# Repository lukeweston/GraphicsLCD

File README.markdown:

Breakout board or interface board for LCD displays.

Intended mainly for KS0108-compatible graphical LCD displays or similar. (Usually 128 x 64 pixels.)

This board allows you to connect a LCD display of this sort to your host microcontroller using a minimal number of pins - and also offloading the processing and memory usage
associated with driving the display away from the host microcontroller and onto the display microcontroller. Based on the Atmel ATmega32U4 (Arduino Leonardo-compatible)
microcontroller.

Serial data is supplied to the microcontroller over either the USB, TTL-level UART, SPI or I2C interfaces - whatever you want. 5V power must also be supplied from the host
microcontroller.

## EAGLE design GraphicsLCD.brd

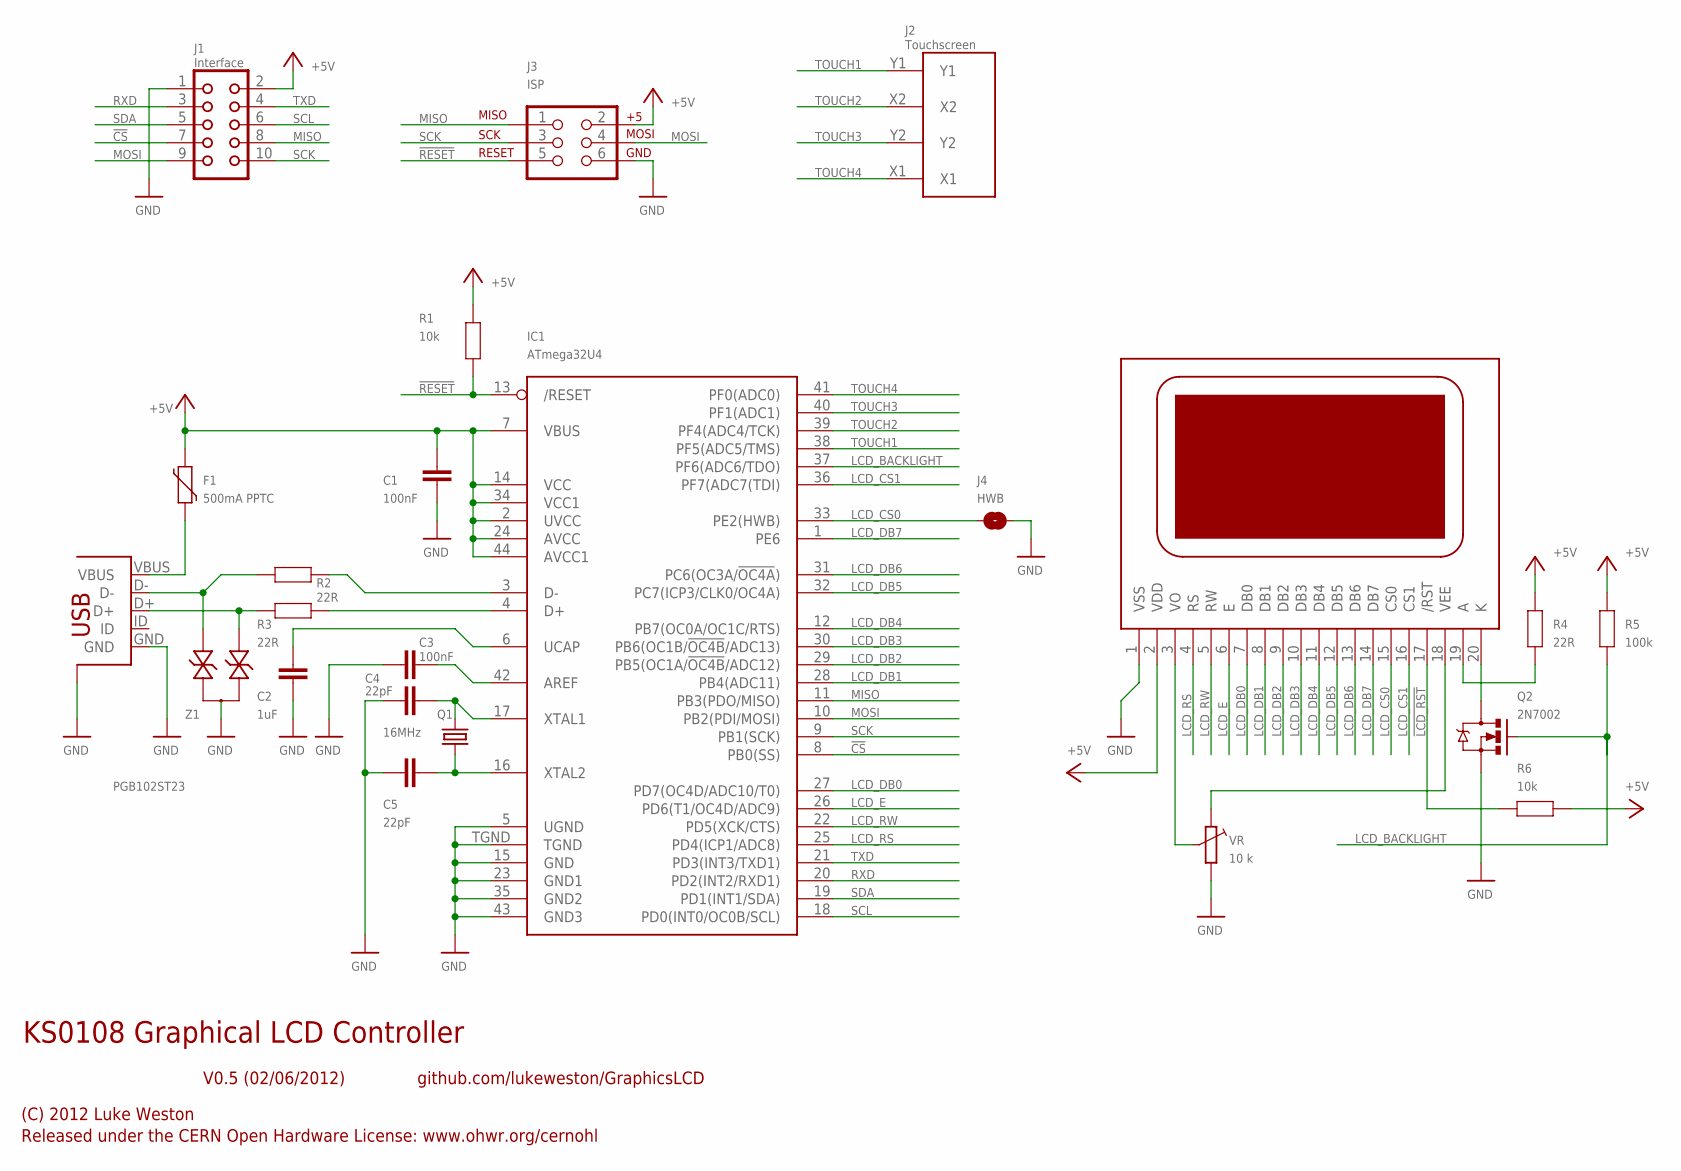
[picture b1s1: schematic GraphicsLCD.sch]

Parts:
C1, C3: 100nF; 0603
C2: 1uF; 0603
C4, C5: 22pF; 0603
F1: 500mA PPTC; 1812
IC1: ATmega32U4; QFN-44N
J1: Interface; CON10
J2: Touchscreen; DS_TOUCH_CONNECTOR
J3: ISP; 2X3-NS
J4: HWB; SJ
J5: USB-FT; USB-MINIB-FT
Q1: 16MHz; HC49US
Q2: 2N7002; SOT23-3
R1, R6: 10k; 0603
R2, R3, R4: 22R; 0603
R5: 100k; 0603
U1: KS0108; TS12864
VR: 10 k; CT6
Z1: PGB102ST23; SOT23-3

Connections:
!CS: IC1.8 (PB0(SS)), J1.7
!LCD_RST: R6.1, U1.17 (/RST)
!RESET: IC1.13 (/RESET), J3.5, R1.1
+5V: C1.2, F1.2, IC1.2 (UVCC), IC1.7 (VBUS), IC1.14 (VCC), IC1.24 (AVCC), IC1.34 (VCC1), IC1.44 (AVCC1), J1.2, J3.2, R1.2, R4.2, R5.2, R6.2, U1.2 (VDD)
A: R4.1, U1.19 (A)
BACKLIGHT_K: Q2.3 (D), U1.20 (K)
GND: C1.1, C2.1, C3.1, C4.1, C5.1, IC1.5 (UGND), IC1.15 (GND), IC1.23 (GND1), IC1.35 (GND2), IC1.43 (GND3), IC1.TGND, J1.1, J3.6, J4.1, J5.GND, J5.SH1 (SH$1), J5.SH2 (SH$1), J5.SH3 (SH$1), J5.SH4 (SH$1), Q2.2 (S), U1.1 (VSS), VR.A, Z1.3
LCD_BACKLIGHT: IC1.37 (PF6(ADC6/TDO)), Q2.1 (G), R5.1
LCD_CS0: IC1.33 (PE2(HWB)), J4.2, U1.15 (CS0)
LCD_CS1: IC1.36 (PF7(ADC7(TDI)), U1.16 (CS1)
LCD_DB0: IC1.27 (PD7(OC4D/ADC10/T0)), U1.7 (DB0)
LCD_DB1: IC1.28 (PB4(ADC11)), U1.8 (DB1)
LCD_DB2: IC1.29 (PB5(OC1A/!OC4B!/ADC12)), U1.9 (DB2)
LCD_DB3: IC1.30 (PB6(OC1B/!OC4B!/ADC13)), U1.10 (DB3)
LCD_DB4: IC1.12 (PB7(OC0A/OC1C/RTS)), U1.11 (DB4)
LCD_DB5: IC1.32 (PC7(ICP3/CLK0/OC4A)), U1.12 (DB5)
LCD_DB6: IC1.31 (PC6(OC3A/!OC4A!)), U1.13 (DB6)
LCD_DB7: IC1.1 (PE6), U1.14 (DB7)
LCD_E: IC1.26 (PD6(T1/OC4D/ADC9)), U1.6 (E)
LCD_RS: IC1.25 (PD4(ICP1/ADC8)), U1.4 (RS)
LCD_RW: IC1.22 (PD5(XCK/CTS)), U1.5 (RW)
LCD_VO: U1.3 (VO), VR.S
MISO: IC1.11 (PB3(PDO/MISO)), J1.8, J3.1
MOSI: IC1.10 (PB2(PDI/MOSI)), J1.9, J3.4
unnamed: F1.1, J5.VBUS
unnamed: C3.2, IC1.42 (AREF)
unnamed: C2.2, IC1.6 (UCAP)
unnamed: J5.D+, R3.2, Z1.1
unnamed: J5.D-, R2.2, Z1.2
unnamed: C4.2, IC1.17 (XTAL1), Q1.2
unnamed: C5.2, IC1.16 (XTAL2), Q1.1
unnamed: IC1.4 (D+), R3.1
unnamed: IC1.3 (D-), R2.1
RXD: IC1.20 (PD2(INT2/RXD1)), J1.3
SCK: IC1.9 (PB1(SCK)), J1.10, J3.3
SCL: IC1.18 (PD0(INT0/OC0B/SCL)), J1.6
SDA: IC1.19 (PD1(INT1/SDA)), J1.5
TOUCH1: IC1.38 (PF5(ADC5/TMS)), J2.Y1
TOUCH2: IC1.39 (PF4(ADC4/TCK)), J2.X2
TOUCH3: IC1.40 (PF1(ADC1)), J2.Y2
TOUCH4: IC1.41 (PF0(ADC0)), J2.X1
TXD: IC1.21 (PD3(INT3/TXD1)), J1.4
VEE: U1.18 (VEE), VR.E

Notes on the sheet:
KS0108 Graphical LCD Controller
V0.5 (02/06/2012)
(C) 2012 Luke Weston
Released under the CERN Open Hardware License: www.ohwr.org/cernohl
github.com/lukeweston/GraphicsLCD

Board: 2 copper layers, 23 parts (0 on the bottom side), 43 nets, no tracks yet.
